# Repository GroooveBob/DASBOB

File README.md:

# DASBOB

36 Key Diodeless Split Choc Keyboard wit a Buzzer 

Firmware:

https://github.com/GroooveBob/DASBOB-qmk

https://codeberg.org/jcowgar/dasbob-36-kmk

https://docs.beekeeb.com/dasbob-keyboard (and layout teste pdf)

Not tested: zmk

special thanks to pcbway for supporting the development

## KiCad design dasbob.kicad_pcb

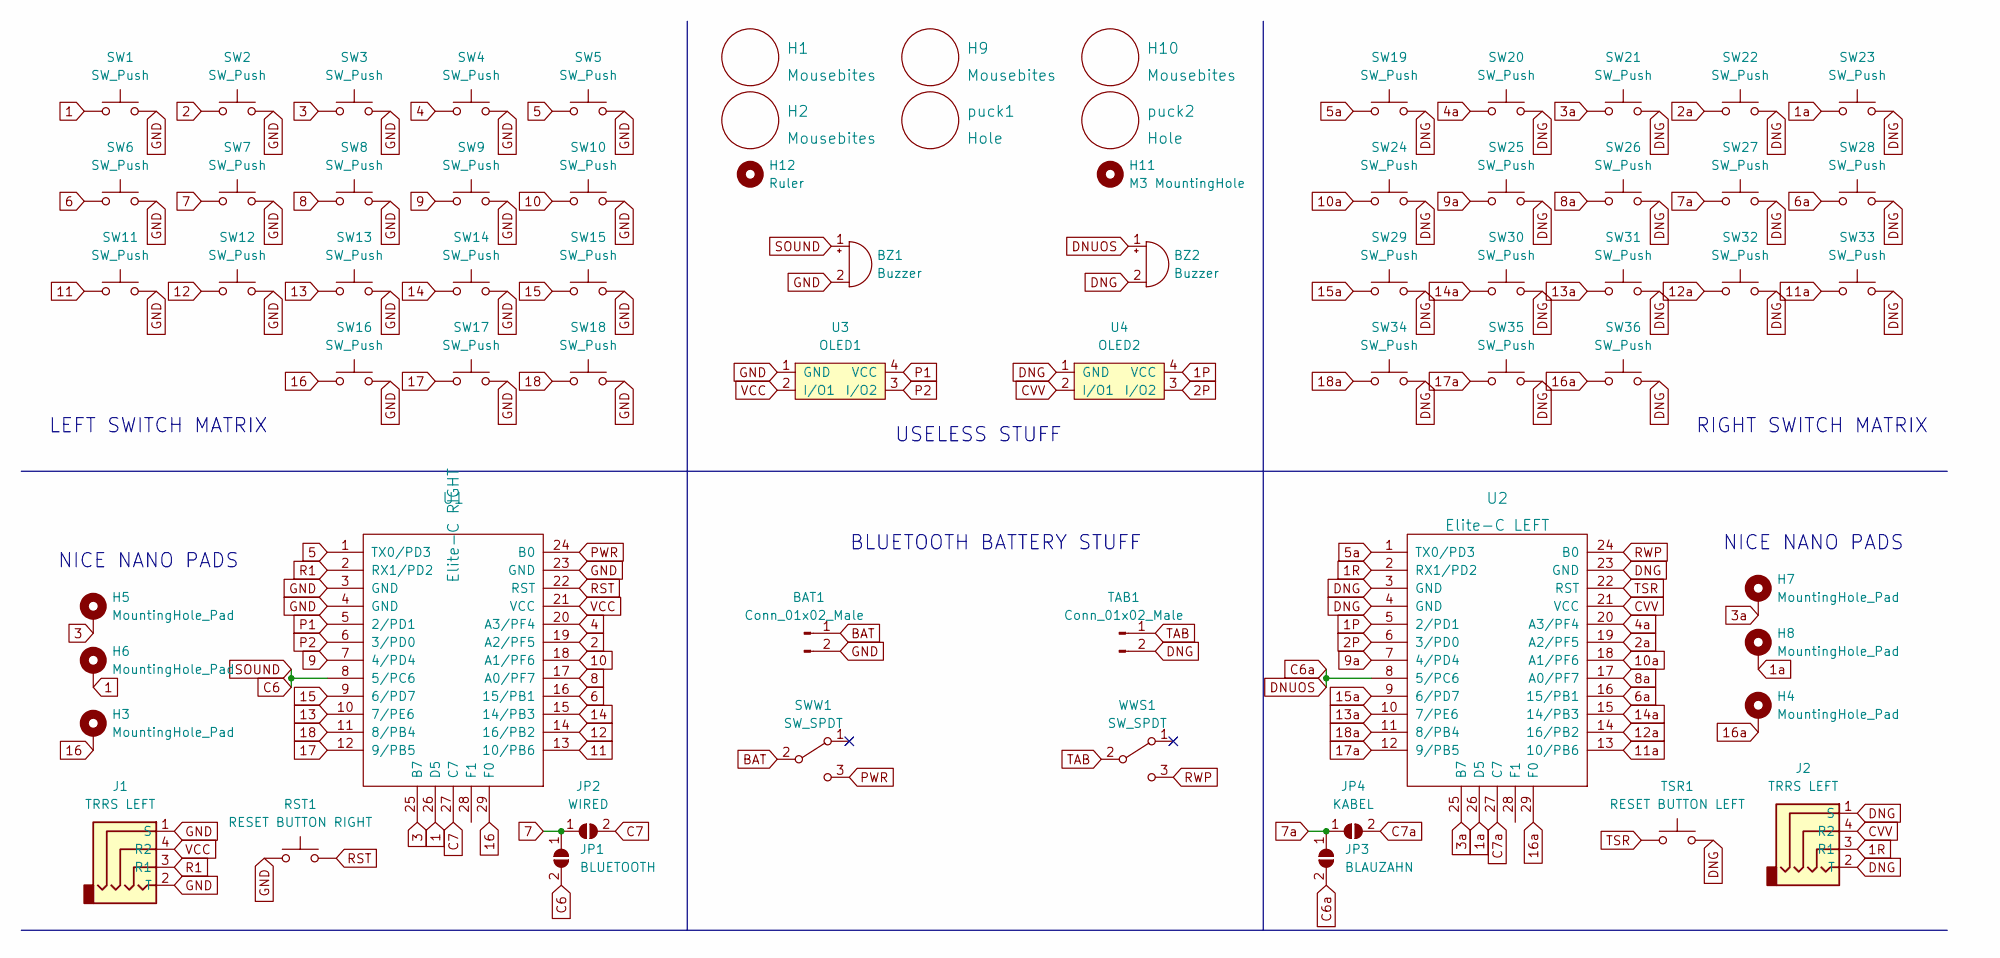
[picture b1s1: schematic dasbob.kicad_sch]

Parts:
BAT1: Conn_01x02_Male; BAT
BZ1, BZ2: Buzzer; Buzzer_Mallory_AST1109MLTRQ
H1, H2, H9, H10: Mousebites; breakaway-mousebites
H3, H4, H5, H6, H7, H8: MountingHole_Pad; SinglePad
H11: M3 MountingHole; MountingHole_2.7mm_M2.5_DIN965
H12: Ruler; Gauge_50mm_Type1_SilkScreenTop
J1, J2: TRRS LEFT; TRRS-PJ-320A
JP1: BLUETOOTH; JUMPER_SMD_2DUB
JP2: WIRED; JUMPER_SMD_2DUB
JP3: BLAUZAHN; JUMPER_SMD_2DUB
JP4: KABEL; JUMPER_SMD_2DUB
RST1: RESET BUTTON RIGHT; ResetSW
SW1, SW2, SW3, SW4, SW5, SW6, SW7, SW8, SW9, SW10, SW11, SW12, SW13, SW14, SW15, SW16, SW17, SW18, SW19, SW20, SW21, SW22, SW23, SW24, SW25, SW26, SW27, SW28, SW29, SW30, SW31, SW32, SW33, SW34, SW35, SW36: SW_Push; Kailh_socket_PG1350_optional
SWW1: SW_SPDT; SW_SPDT_PCM12
TAB1: Conn_01x02_Male; BAT
TSR1: RESET BUTTON LEFT; ResetSW
U1: Elite-C RIGHT; Elite-C
U2: Elite-C LEFT; Elite-C
U3: OLED1; I2C_Breakout
U4: OLED2; I2C_Breakout
WWS1: SW_SPDT; SW_SPDT_PCM12
puck1, puck2: Hole; Tenting_Puck

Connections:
1: H6.1, SW1.1, U1.26 (D5)
1P: U2.5 (2/PD1), U4.4 (VCC)
1R: J2.3 (R1), U2.2 (RX1/PD2)
1a: H8.1, SW23.1, U2.26 (D5)
2: SW2.1, U1.19 (A2/PF5)
2P: U2.6 (3/PD0), U4.3 (I/O2)
2a: SW22.1, U2.19 (A2/PF5)
3: H5.1, SW3.1, U1.25 (B7)
3a: H7.1, SW21.1, U2.25 (B7)
4: SW4.1, U1.20 (A3/PF4)
4a: SW20.1, U2.20 (A3/PF4)
5: SW5.1, U1.1 (TX0/PD3)
5a: SW19.1, U2.1 (TX0/PD3)
6: SW6.1, U1.16 (15/PB1)
6a: SW28.1, U2.16 (15/PB1)
7: JP1.1 (A), JP2.1 (A), SW7.1
7a: JP3.1 (A), JP4.1 (A), SW27.1
8: SW8.1, U1.17 (A0/PF7)
8a: SW26.1, U2.17 (A0/PF7)
9: SW9.1, U1.7 (4/PD4)
9a: SW25.1, U2.7 (4/PD4)
10: SW10.1, U1.18 (A1/PF6)
10a: SW24.1, U2.18 (A1/PF6)
11: SW11.1, U1.13 (10/PB6)
11a: SW33.1, U2.13 (10/PB6)
12: SW12.1, U1.14 (16/PB2)
12a: SW32.1, U2.14 (16/PB2)
13: SW13.1, U1.10 (7/PE6)
13a: SW31.1, U2.10 (7/PE6)
14: SW14.1, U1.15 (14/PB3)
14a: SW30.1, U2.15 (14/PB3)
15: SW15.1, U1.9 (6/PD7)
15a: SW29.1, U2.9 (6/PD7)
16: H3.1, SW16.1, U1.29 (F0)
16a: H4.1, SW36.1, U2.29 (F0)
17: SW17.1, U1.12 (9/PB5)
17a: SW35.1, U2.12 (9/PB5)
18: SW18.1, U1.11 (8/PB4)
18a: SW34.1, U2.11 (8/PB4)
BAT: BAT1.1, SWW1.2 (B)
C7: JP2.2 (B), U1.27 (C7)
C7a: JP4.2 (B), U2.27 (C7)
CVV: J2.4 (R2), U2.21 (VCC), U4.2 (I/O1)
DNG: BZ2.2 (+), J2.1 (S), J2.2 (T), SW19.2, SW20.2, SW21.2, SW22.2, SW23.2, SW24.2, SW25.2, SW26.2, SW27.2, SW28.2, SW29.2, SW30.2, SW31.2, SW32.2, SW33.2, SW34.2, SW35.2, SW36.2, TAB1.2, TSR1.2, U2.3 (GND), U2.4 (GND), U2.23 (GND), U4.1 (GND)
DNUOS: BZ2.1 (-), JP3.2 (B), U2.8 (5/PC6)
GND: BAT1.2, BZ1.2 (+), J1.1 (S), J1.2 (T), RST1.1, SW1.2, SW2.2, SW3.2, SW4.2, SW5.2, SW6.2, SW7.2, SW8.2, SW9.2, SW10.2, SW11.2, SW12.2, SW13.2, SW14.2, SW15.2, SW16.2, SW17.2, SW18.2, U1.3 (GND), U1.4 (GND), U1.23 (GND), U3.1 (GND)
P1: U1.5 (2/PD1), U3.4 (VCC)
P2: U1.6 (3/PD0), U3.3 (I/O2)
PWR: SWW1.3 (C), U1.24 (B0)
R1: J1.3 (R1), U1.2 (RX1/PD2)
RST: RST1.2, U1.22 (RST)
RWP: U2.24 (B0), WWS1.3 (C)
SOUND: BZ1.1 (-), JP1.2 (B), U1.8 (5/PC6)
TAB: TAB1.1, WWS1.2 (B)
TSR: TSR1.1, U2.22 (RST)
VCC: J1.4 (R2), U1.21 (VCC), U3.2 (I/O1)

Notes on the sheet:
RIGHT SWITCH MATRIX
NICE NANO PADS
USELESS STUFF
LEFT SWITCH MATRIX
BLUETOOTH BATTERY STUFF

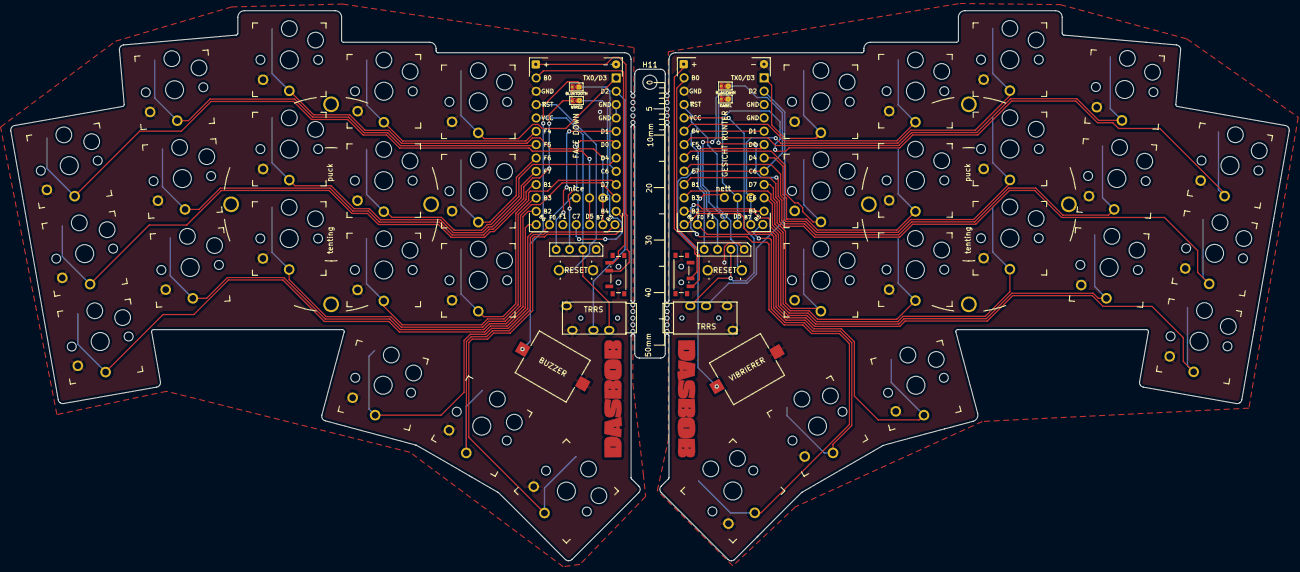
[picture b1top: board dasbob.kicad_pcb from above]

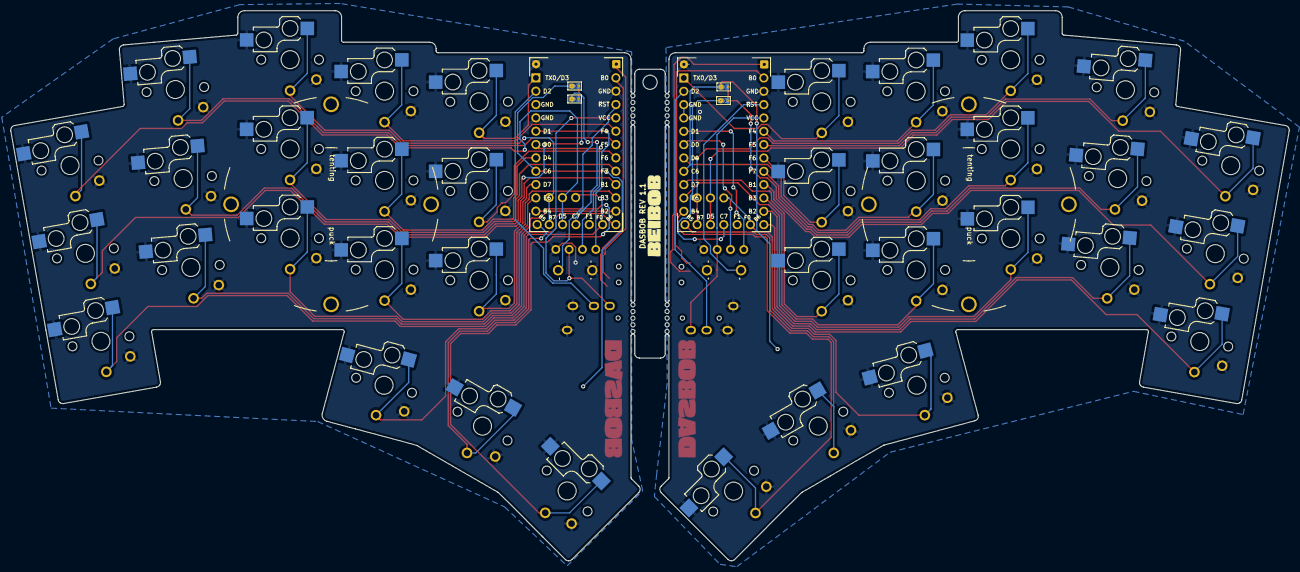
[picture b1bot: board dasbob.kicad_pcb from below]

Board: 2 copper layers, 243.5 x 104.8 mm, 68 parts (2 on the bottom side), 56 nets.

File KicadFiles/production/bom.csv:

Designator,Footprint,Quantity,Value,LCSC Part #
SW12,Kailh_socket_PG1350_optional,1,SW_Push,
SW18,Kailh_socket_PG1350_optional,1,SW_Push,
SW19,Kailh_socket_PG1350_optional,1,SW_Push,
SW15,Kailh_socket_PG1350_optional,1,SW_Push,
WWS1,SW_SPDT_PCM12,1,SW_SPDT,
SW23,Kailh_socket_PG1350_optional,1,SW_Push,
SW28,Kailh_socket_PG1350_optional,1,SW_Push,
JP1,JUMPER_SMD_2DUB,1,BLUETOOTH,
SW4,Kailh_socket_PG1350_optional,1,SW_Push,
SW17,Kailh_socket_PG1350_optional,1,SW_Push,
U3,I2C_Breakout,1,OLED1,
U4,I2C_Breakout,1,OLED2,
SW16,Kailh_socket_PG1350_optional,1,SW_Push,
H6,SinglePad,1,MountingHole_Pad,
SW32,Kailh_socket_PG1350_optional,1,SW_Push,
J2,TRRS-PJ-320A,1,TRRS LEFT,
SW24,Kailh_socket_PG1350_optional,1,SW_Push,
SW35,Kailh_socket_PG1350_optional,1,SW_Push,
puck2,Tenting_Pucksmol,1,Hole,
puck1,Tenting_Pucksmol,1,Hole,
SW3,Kailh_socket_PG1350_optional,1,SW_Push,
H2,breakaway-mousebites,1,Mousebites,
RST1,SW_ResetSW,1,SW_Push,
SW22,Kailh_socket_PG1350_optional,1,SW_Push,
H3,SinglePad,1,MountingHole_Pad,
SWW1,SW_SPDT_PCM12,1,SW_SPDT,
JP2,JUMPER_SMD_2DUB,1,WIRED,
SW34,Kailh_socket_PG1350_optional,1,SW_Push,
SW20,Kailh_socket_PG1350_optional,1,SW_Push,
SW30,Kailh_socket_PG1350_optional,1,SW_Push,
SW6,Kailh_socket_PG1350_optional,1,SW_Push,
BZ1,Buzzer_Mallory_AST1109MLTRQ,1,Buzzer,
SW10,Kailh_socket_PG1350_optional,1,SW_Push,
BZ2,Buzzer_Mallory_AST1109MLTRQ,1,Buzzer,
SW7,Kailh_socket_PG1350_optional,1,SW_Push,
SW27,Kailh_socket_PG1350_optional,1,SW_Push,
JP3,JUMPER_SMD_2DUB,1,BLAUZAHN,
SW25,Kailh_socket_PG1350_optional,1,SW_Push,
SW13,Kailh_socket_PG1350_optional,1,SW_Push,
SW29,Kailh_socket_PG1350_optional,1,SW_Push,
TSR1,SW_ResetSW,1,SW_Push,
H4,SinglePad,1,MountingHole_Pad,
SW11,Kailh_socket_PG1350_optional,1,SW_Push,
SW1,Kailh_socket_PG1350_optional,1,SW_Push,
SW2,Kailh_socket_PG1350_optional,1,SW_Push,
H5,SinglePad,1,MountingHole_Pad,
H10,breakaway-mousebites,1,Mousebites,
SW9,Kailh_socket_PG1350_optional,1,SW_Push,
BAT1,BAT,1,Conn_01x02_Male,
J1,TRRS-PJ-320A,1,TRRS LEFT,
H9,breakaway-mousebites,1,Mousebites,
JP4,JUMPER_SMD_2DUB,1,KABEL,
SW36,Kailh_socket_PG1350_optional,1,SW_Push,
H1,breakaway-mousebites,1,Mousebites,
H7,SinglePad,1,MountingHole_Pad,
SW5,Kailh_socket_PG1350_optional,1,SW_Push,
H12,Gauge_50mm_Type1_SilkScreenTop,1,Ruler,
TAB1,BAT,1,Conn_01x02_Male,
SW33,Kailh_socket_PG1350_optional,1,SW_Push,
SW14,Kailh_socket_PG1350_optional,1,SW_Push,
SW31,Kailh_socket_PG1350_optional,1,SW_Push,
H11,MountingHole_2.7mm_M2.5_DIN965,1,M3 MountingHole,
SW8,Kailh_socket_PG1350_optional,1,SW_Push,
SW26,Kailh_socket_PG1350_optional,1,SW_Push,
H8,SinglePad,1,MountingHole_Pad,
SW21,Kailh_socket_PG1350_optional,1,SW_Push,
U1,Elite-C,1,Elite-C RIGHT,
U2,Elite-C,1,Elite-C LEFT,

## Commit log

2022-08-11 here we go
2022-08-11 image
2022-08-11 v1.1
2022-08-11 rev1.1
2022-08-12 moved thumbs 1mm down
2022-08-12 keymap changed
2022-08-14 routed the oled to the wrong pins because im a ducking idiot now i fixed it
2022-09-17 buzzer was not working
    buzzer was not working put a jumper for it on the board
2022-09-29 Create LICENSE
2022-11-09 ground issues
2023-08-11 fix copper layers
